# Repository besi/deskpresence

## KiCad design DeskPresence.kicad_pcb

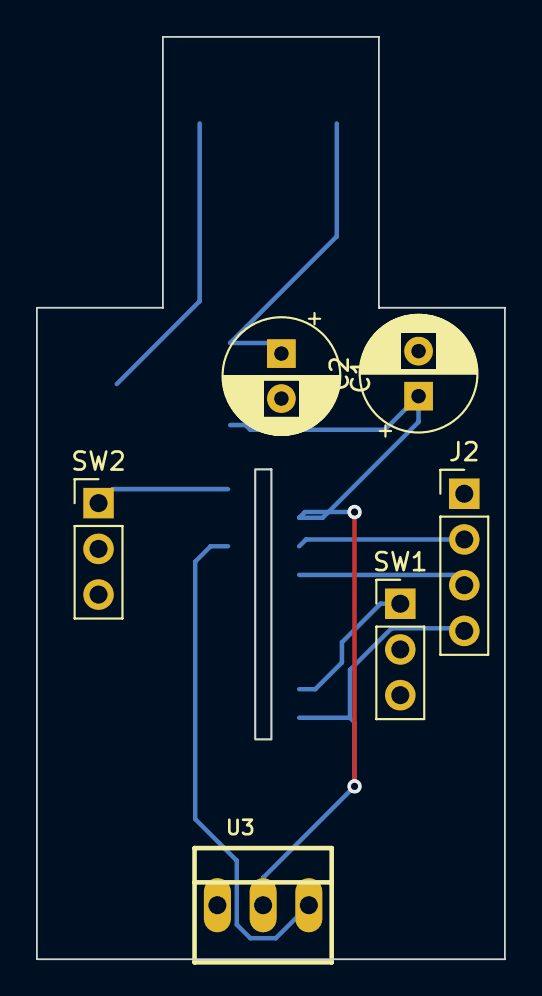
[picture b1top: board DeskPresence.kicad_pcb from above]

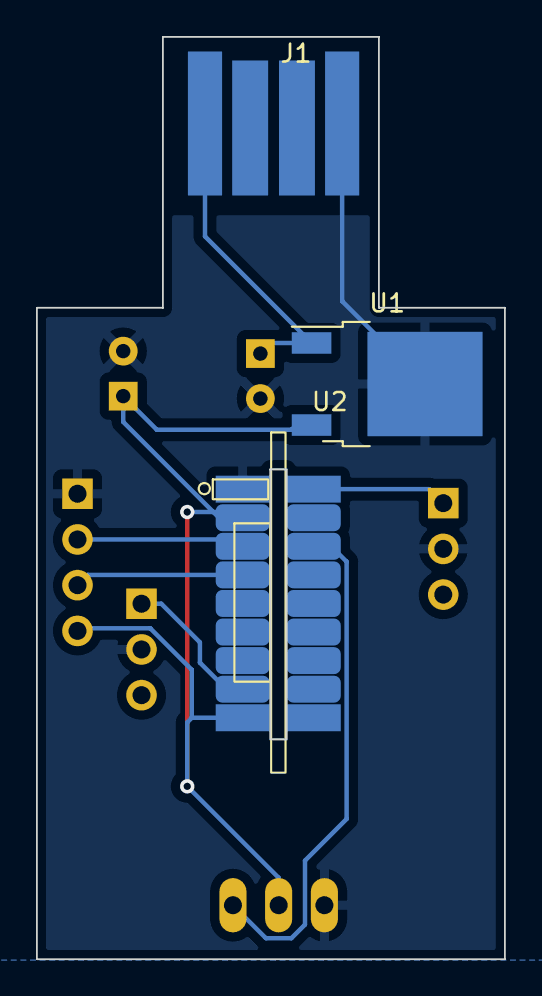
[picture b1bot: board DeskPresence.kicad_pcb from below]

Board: 2 copper layers, 26.0 x 51.2 mm, 9 parts (3 on the bottom side), 8 nets.

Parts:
C1, C2: C_Polarized; CP_Radial_D6.3mm_P2.50mm
J1: USB_A; usb-a-pcb
J2: TTL; PinHeader_1x04_P2.54mm_Vertical
SW1: MODE; PinHeader_1x03_P2.54mm_Vertical
SW2: RESET; PinHeader_1x03_P2.54mm_Vertical
U1: UA78M33_TO252; TO-252-2
U2: esp-01m
U3: GP2Y0A02YK0F

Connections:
+3V3: C2.1, J2.4 (VDD), U1.3 (VO), U2.2 (VDD), U2.9 (EN), U3.2 (VCC)
+5V: C1.1, J1.1 (VBUS), U1.1 (VI)
/Data: U2.16 (ADC), U3.3 (VOUT)
GND: C1.2, C2.2, J1.4 (GND), J2.1 (GND), SW1.2, SW2.2, U1.2 (GND), U2.1 (GND), U3.1 (GND)
unnamed: SW1.1, U2.8 (GP0)
unnamed: SW2.1, U2.18 (RST)
RX: J2.3 (TX), U2.4 (GP3/RX)
TX: J2.2 (RX), U2.3 (GP2/TX)

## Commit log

2023-11-25 Add software
2023-11-25 Add empty kicad project
2023-11-28 Add raw pcb with USB-A connector
2023-12-29 Sketchy first pcb
2024-02-13 Add touch file
